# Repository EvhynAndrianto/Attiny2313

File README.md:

# Attiny2313
Everything you might need for building Attiny2313 based microcontroller project.

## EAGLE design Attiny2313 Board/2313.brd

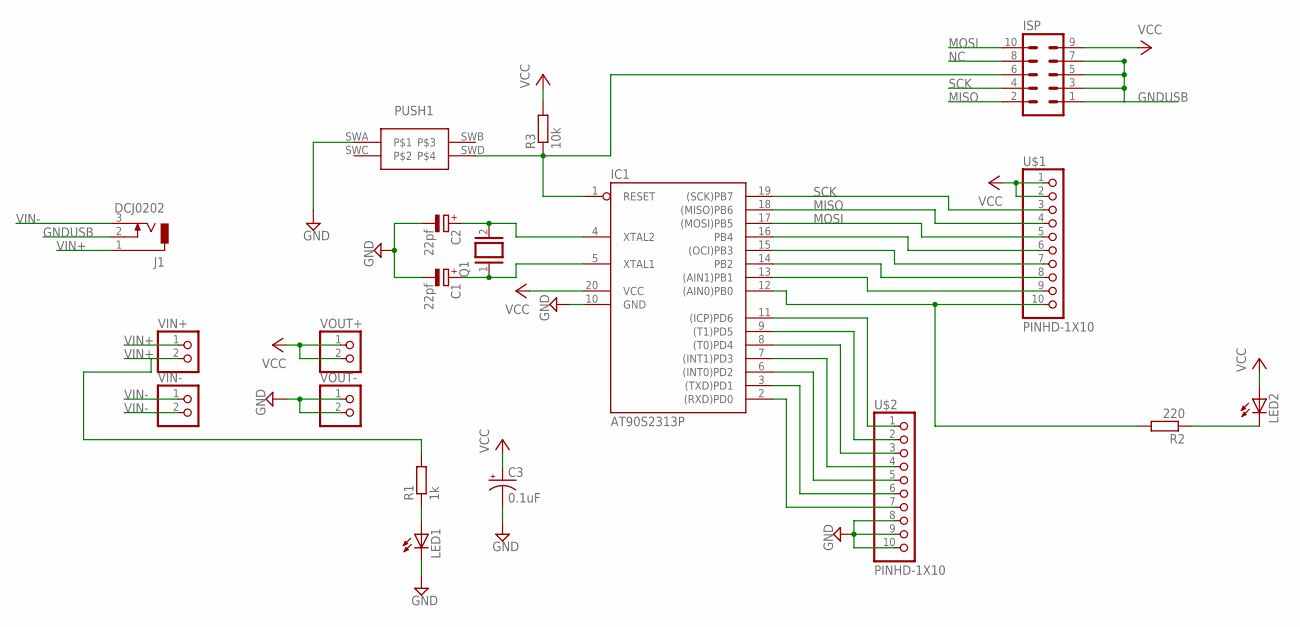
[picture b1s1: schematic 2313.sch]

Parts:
C1, C2: 22pf; E1,8-4
C3: 0.1uF; E1,8-4
IC1: AT90S2313P; DIL20
ISP: MA05-2
J1: DCJ0202
LED1, LED2: LED3MM
PUSH1: PUSH_BUTTON
Q1: XTAL; Q
R1: 1k; 0204/7
R2: 220; 0204/7
R3: 10k; 0204/7
U$1, U$2: PINHD-1X10; 1X10-BIG
VIN+: PINHD-1X2; 1X02
VIN-: PINHD-1X2; 1X02
VOUT+: PINHD-1X2; 1X02
VOUT-: PINHD-1X2; 1X02

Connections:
GND: C1.-, C2.-, C3.-, IC1.10 (GND), LED1.K (C), PUSH1.SWA, U$2.8, U$2.9, U$2.10, VOUT-.1, VOUT-.2
GNDUSB: ISP.1, ISP.3, ISP.5, ISP.7, J1.2
MISO: IC1.18 ((MISO)PB6), ISP.2, U$1.4
MOSI: IC1.17 ((MOSI)PB5), ISP.10, U$1.5
unnamed: C1.+, IC1.5 (XTAL1), Q1.1
unnamed: C2.+, IC1.4 (XTAL2), Q1.2
unnamed: IC1.1 (RESET), ISP.6, PUSH1.SWD, R3.1
unnamed: IC1.11 ((ICP)PD6), U$2.1
unnamed: IC1.13 ((AIN1)PB1), U$1.9
unnamed: IC1.14 (PB2), U$1.8
unnamed: IC1.15 ((OCI)PB3), U$1.7
unnamed: IC1.16 (PB4), U$1.6
unnamed: IC1.12 ((AIN0)PB0), R2.2, U$1.10
unnamed: IC1.9 ((T1)PD5), U$2.2
unnamed: IC1.8 ((T0)PD4), U$2.3
unnamed: IC1.7 ((INT1)PD3), U$2.4
unnamed: IC1.6 ((INT0)PD2), U$2.5
unnamed: IC1.3 ((TXD)PD1), U$2.6
unnamed: IC1.2 ((RXD)PD0), U$2.7
unnamed: LED1.A, R1.1
unnamed: LED2.K (C), R2.1
NC: ISP.8
SCK: IC1.19 ((SCK)PB7), ISP.4, U$1.3
VCC: C3.+, IC1.20 (VCC), ISP.9, LED2.A, R3.2, U$1.1, U$1.2, VOUT+.1, VOUT+.2
VIN+: J1.1, R1.2, VIN+.1, VIN+.2
VIN-: J1.3, VIN-.1, VIN-.2

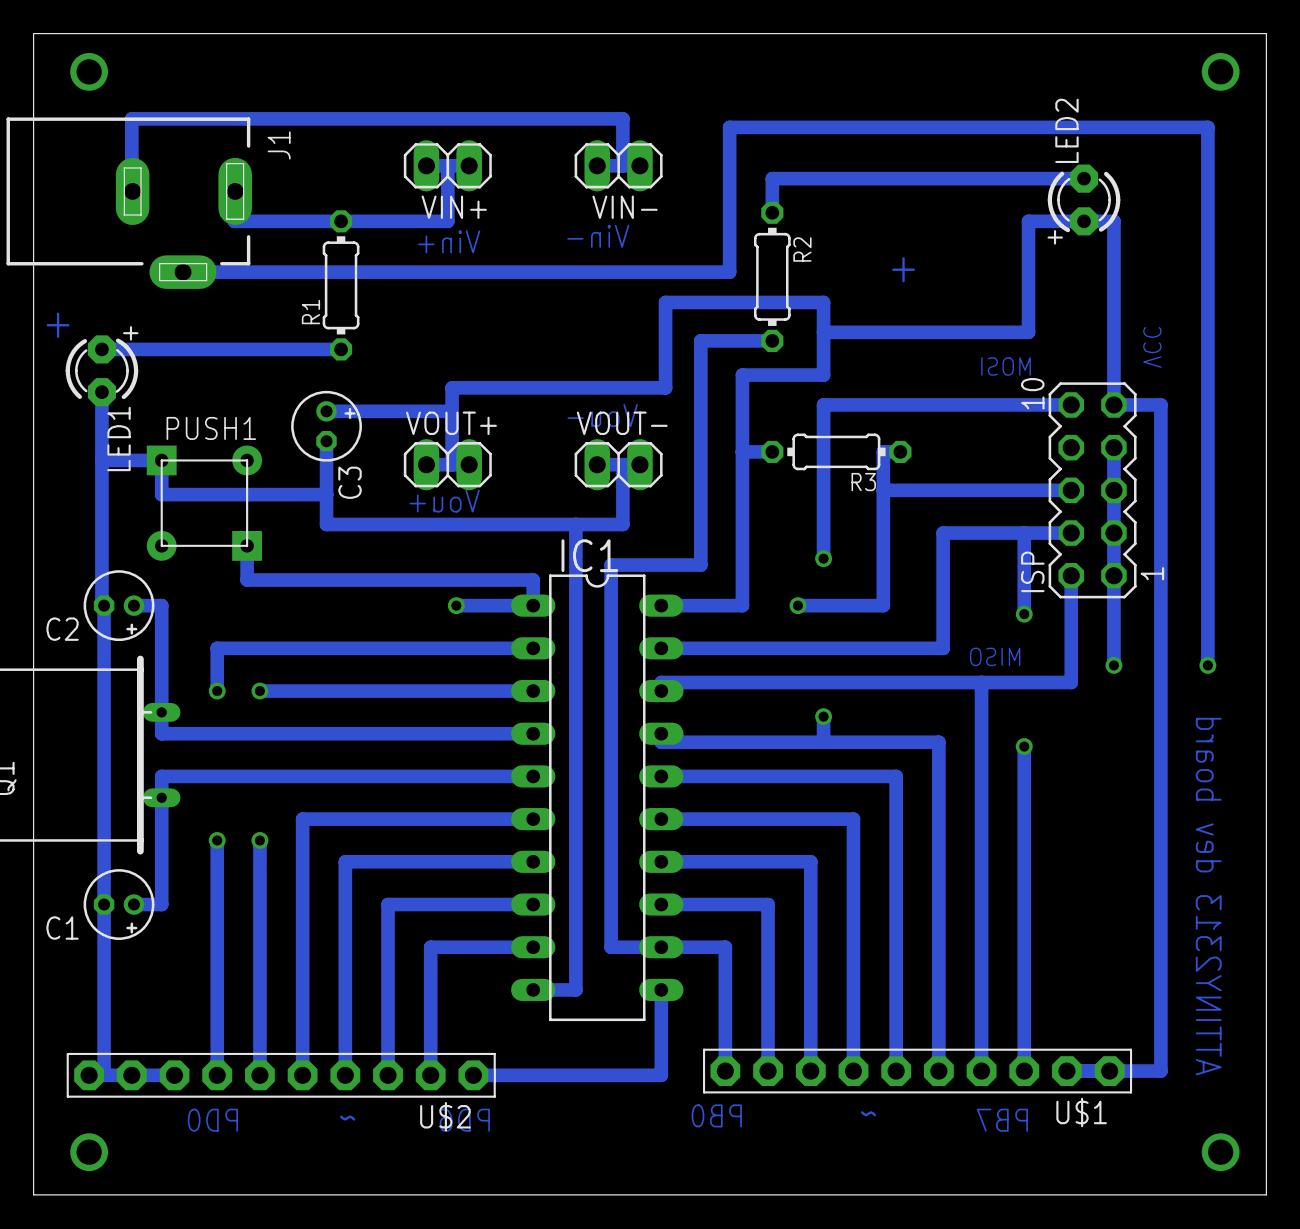
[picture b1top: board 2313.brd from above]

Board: 2 copper layers, 73.3 x 69.1 mm, 19 parts (0 on the bottom side), 25 nets.

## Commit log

2017-12-29 Create LICENSE
